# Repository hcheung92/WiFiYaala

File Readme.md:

WiFi Yaala
==========
Yaala = Yet Another Ambient Light Approach using an ESP8622 chip

Background
----------
Despite some early prototypes this is the third major attempt to create a fully featured and yet simple to control RGB LED system.  

Project Status
--------------
As a base we are using the nodeMCU core to provide a fully functional eLUA console. We are adding stuff specific for our application like a LED core.
Additionally, we add some optional nice to have features like the Domain Name support for the DHCP client.

It is currently in a VERY early state. Documentation does not yet exist. The only thing which is working right now is the driver support for APA102 and PCA9685 LEDs. Besides others, WS28XX LEDs (glitch free, using hardware support) are getting implemented right now.
Stay tuned...

Features
--------

1) Removed eLUA (nodemcu) modules
- PWM: we need the timer for the LEDs
- MQTT: currently no needed
- WS2812: we are doing it proper: 127bytes hardware FIFO support. No hitches or glitches...

2) Embedded web browser
/fsbrowse let's you browse the file system
/lua HTTP POST requests get interpreted. See lua/luaexec.html for more details on this.

3) Additional LUA stuff
- hostname.set() / hostname.get() let's you specify a hostname that will be transmitted to the DHCP server during a DHCP request. Execute the command BEFORE getting/renewing an IP, e.g. in the first line of init.lua
- led.XXXX see lua-folder and/or sourcecode for usage (for now, I am too lazy to document it ggg)

Requirements
-------------
GCC toolchain, see https://github.com/esp8266/esp8266-wiki/wiki

Building
--------
Goto firmware-lua and type "make && make flash"

Credits
----------
This work is based  on:

- Espressif SDK (http://bbs.espressif.com/viewforum.php?f=5)
- NodeMCU (https://github.com/nodemcu/nodemcu-firmware)
- eLUA (http://www.eluaproject.net/)
- and various other unnamed contributors

Due to frequent major changes in the code---especially in the SDK---everything is copied into this repo.

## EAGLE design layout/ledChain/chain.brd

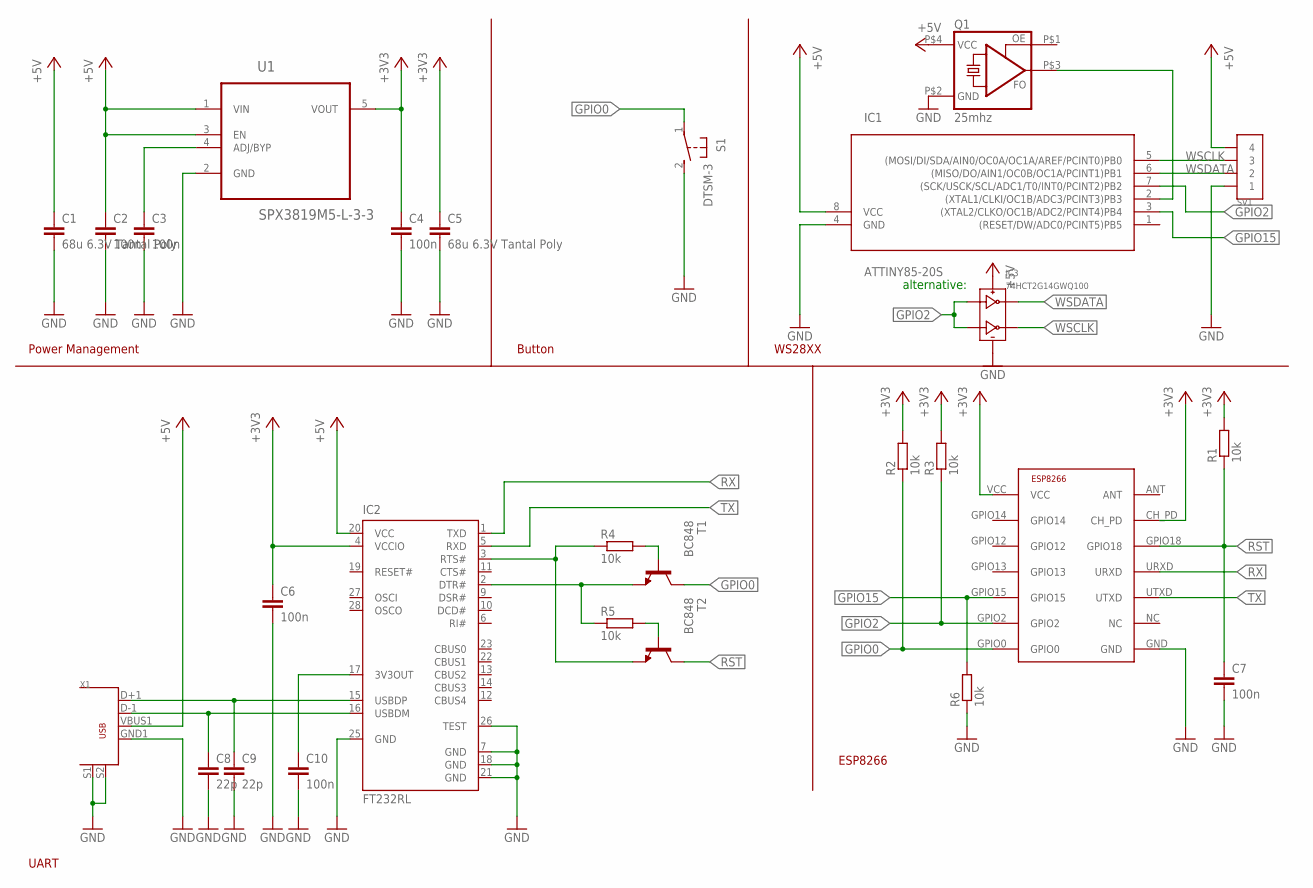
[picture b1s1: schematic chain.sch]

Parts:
C1, C5: 68u 6.3V Tantal Poly; C0805
C2, C3, C4, C6, C7, C10: 100n; C0603
C8, C9: 22p; C0603
IC1: ATTINY85-20S; SOIC8
IC2: FT232RL; SSOP28
IC3: 74HCT2G14GWQ100; SOT363
Q1: 25mhz; KC5032A
R1, R2, R3, R4, R5, R6: 10k; R0603
S1: DTSM-3
SV1: 1X4SMD-2.54LIEGEND
T1, T2: BC848; SOT23
U1: SPX3819M5-L-3-3; SOT95P280X145-5N
U$2: ESP8266; ESP-03
X1: USB-MALE-SMT

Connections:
+3V3: C4.1, C5.1, C6.1, IC2.4 (VCCIO), R1.2, R2.2, R3.2, U1.5 (VOUT), U$2.CH_PD, U$2.VCC
+5V: C1.1, C2.1, IC1.8 (VCC), IC2.20 (VCC), IC3.5 (VCC), Q1.P$4 (VCC), SV1.P$4 (4), U1.1 (VIN), U1.3 (EN), X1.VBUS1 (VBUS)
GND: C1.2, C2.2, C3.2, C4.2, C5.2, C6.2, C7.2, C8.2, C9.2, C10.2, IC1.4 (GND), IC2.7 (GND), IC2.18 (GND), IC2.21 (GND), IC2.25 (GND), IC2.26 (TEST), IC3.2 (GND), Q1.P$2 (GND), R6.1, S1.2, SV1.P$1 (1), U1.2 (GND), U$2.GND, X1.GND1 (GND), X1.S1, X1.S2
GPIO0: R2.1, S1.1, T1.3 (C), U$2.GPIO0
GPIO2: IC1.7 ((SCK/USCK/SCL/ADC1/T0/INT0/PCINT2)PB2), IC3.1 (1A), IC3.3 (2A), R3.1, U$2.GPIO2
GPIO15: IC1.3 ((XTAL2/CLKO/OC1B/ADC2/PCINT4)PB4), R6.2, U$2.GPIO15
unnamed: IC2.3 (RTS#), R4.1, T2.2 (E)
unnamed: IC1.2 ((XTAL1/CLKI/OC1B/ADC3/PCINT3)PB3), Q1.P$3 (FO)
unnamed: C9.1, IC2.15 (USBDP), X1.D+1 (D+)
unnamed: C8.1, IC2.16 (USBDM), X1.D-1 (D-)
unnamed: IC2.2 (DTR#), R5.1, T1.2 (E)
unnamed: R4.2, T1.1 (B)
unnamed: R5.2, T2.1 (B)
unnamed: C10.1, IC2.17 (3V3OUT)
unnamed: C3.1, U1.4 (ADJ/BYP)
RST: C7.1, R1.1, T2.3 (C), U$2.GPIO18
RX: IC2.1 (TXD), U$2.URXD
TX: IC2.5 (RXD), U$2.UTXD
WSCLK: IC1.5 ((MOSI/DI/SDA/AIN0/OC0A/OC1A/AREF/PCINT0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), IC3.4 (2Y), SV1.P$3 (3)
WSDATA: IC1.6 ((MISO/DO/AIN1/OC0B/OC1A/PCINT1)PB1), IC3.6 (1Y), SV1.P$2 (2)

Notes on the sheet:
Power Management
Button
UART
ESP8266
WS28XX
alternative:

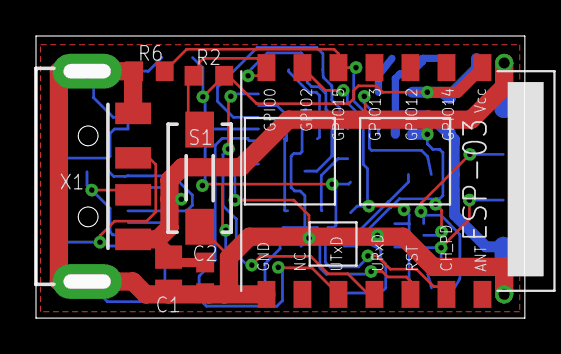
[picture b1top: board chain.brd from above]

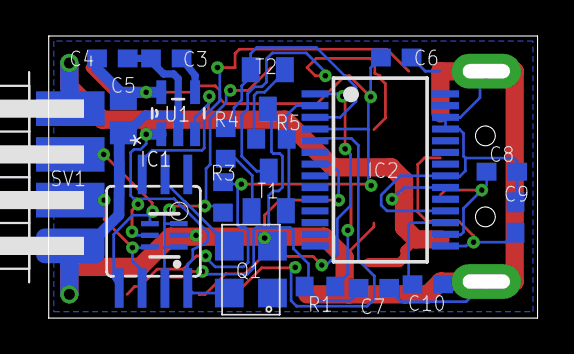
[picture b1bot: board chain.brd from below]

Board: 2 copper layers, 27.2 x 15.7 mm, 27 parts (20 on the bottom side), 20 nets.

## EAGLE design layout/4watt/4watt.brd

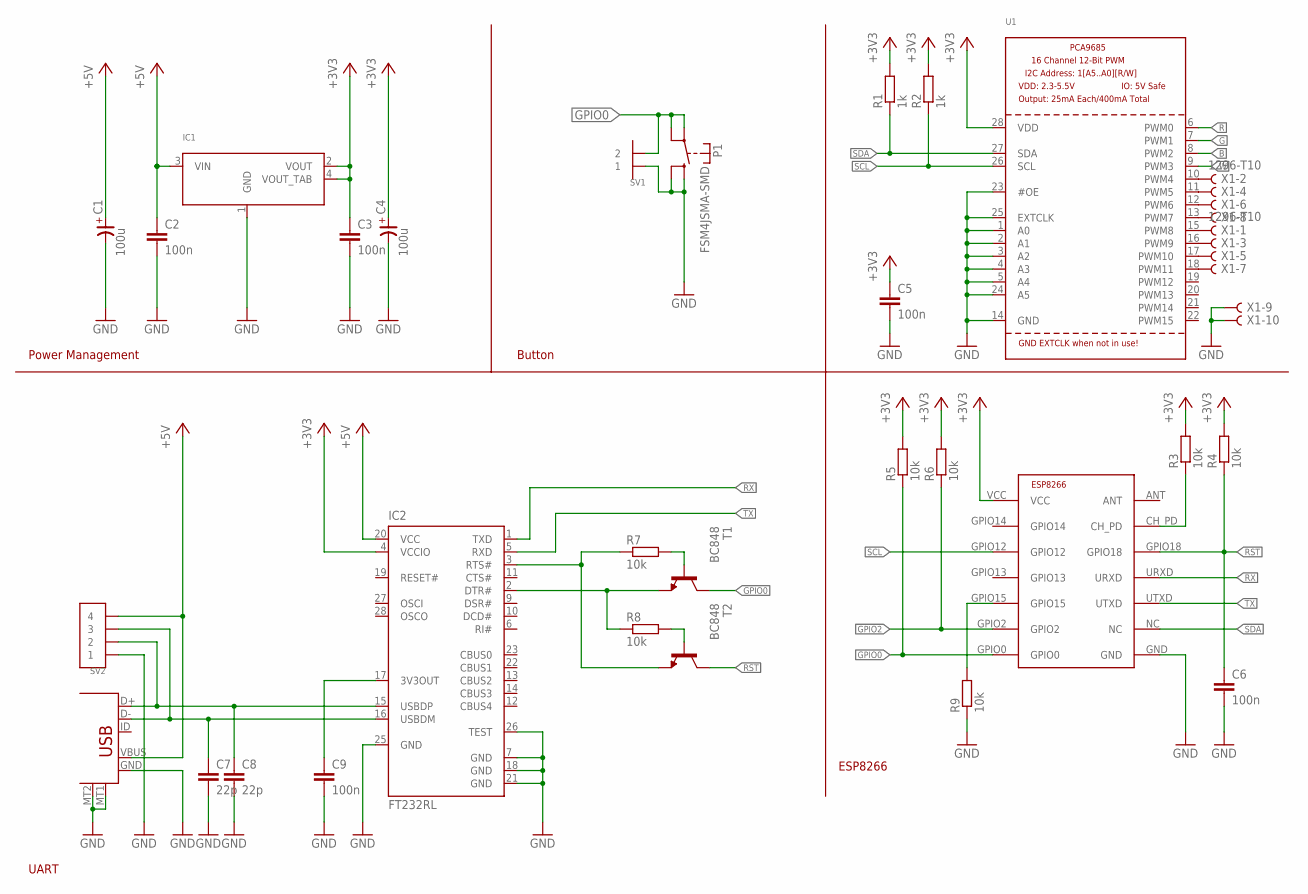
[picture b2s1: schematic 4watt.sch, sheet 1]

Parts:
C1, C4: 100u; 7343-TE-D
C2, C3, C5, C6, C9: 100n; C0603
C7, C8: 22p; C0603
IC1: LM1117IMP; SOT223
IC2: FT232RL; SSOP28
P1: FSM4JSMA-SMD
R1, R2: 1k; R0603
R3, R4, R5, R6, R7, R8, R9: 10k; R0603
SV1: 1X2SMD-2.54LIEGEND
SV2: 1X4SMD-2.54LIEGEND
T1, T2: BC848; SOT23
U1: PCA9685; TSSOP28
U$1: ESP8266; ESP-03
X1: 1296-T10; 1296-10
X2: USB-B; USB-MICROB

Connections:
+3V3: C3.1, C4.+, C5.1, IC1.2 (VOUT), IC1.4 (VOUT_TAB), IC2.4 (VCCIO), R1.2, R2.2, R3.2, R4.2, R5.2, R6.2, U1.28 (VDD), U$1.VCC
+5V: C1.+, C2.1, IC1.3 (VIN), IC2.20 (VCC), SV2.P$4 (4), X2.VBUS; also elsewhere on the board
B: U1.8 (PWM2); also elsewhere on the board
G: U1.7 (PWM1); also elsewhere on the board
GND: C1.-, C2.2, C3.2, C4.-, C5.2, C6.2, C7.2, C8.2, C9.2, IC1.1 (GND), IC2.7 (GND), IC2.18 (GND), IC2.21 (GND), IC2.25 (GND), IC2.26 (TEST), P1.P$3 (S), P1.P$4 (S), R9.1, SV1.P$1 (1), SV2.P$1 (1), U1.1 (A0), U1.2 (A1), U1.3 (A2), U1.4 (A3), U1.5 (A4), U1.14 (GND), U1.23 (#OE), U1.24 (A5), U1.25 (EXTCLK), U$1.GND, X1.9, X1.10, X2.GND, X2.MT1, X2.MT2; also elsewhere on the board
GPIO0: P1.P$1, P1.P$2, R5.1, SV1.P$2 (2), T1.3 (C), U$1.GPIO0
GPIO2: R6.1, U$1.GPIO2; also elsewhere on the board
GPIO15: R9.2, U$1.GPIO15
unnamed: IC2.3 (RTS#), R7.1, T2.2 (E)
unnamed: R3.1, U$1.CH_PD
unnamed: C8.1, IC2.15 (USBDP), SV2.P$2 (2), X2.D+
unnamed: C7.1, IC2.16 (USBDM), SV2.P$3 (3), X2.D-
unnamed: IC2.2 (DTR#), R8.1, T1.2 (E)
unnamed: R7.2, T1.1 (B)
unnamed: R8.2, T2.1 (B)
unnamed: C9.1, IC2.17 (3V3OUT)
unnamed: U1.10 (PWM4), X1.2
unnamed: U1.11 (PWM5), X1.4
unnamed: U1.12 (PWM6), X1.6
unnamed: U1.13 (PWM7), X1.8
unnamed: U1.15 (PWM8), X1.1
unnamed: U1.16 (PWM9), X1.3
unnamed: U1.17 (PWM10), X1.5
unnamed: U1.18 (PWM11), X1.7
R: U1.6 (PWM0); also elsewhere on the board
RST: C6.1, R4.1, T2.3 (C), U$1.GPIO18
RX: IC2.1 (TXD), U$1.URXD
SCL: R2.1, U1.26 (SCL), U$1.GPIO12
SDA: R1.1, U1.27 (SDA), U$1.NC
TX: IC2.5 (RXD), U$1.UTXD
W: U1.9 (PWM3); also elsewhere on the board

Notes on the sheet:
Power Management
Button
UART
ESP8266

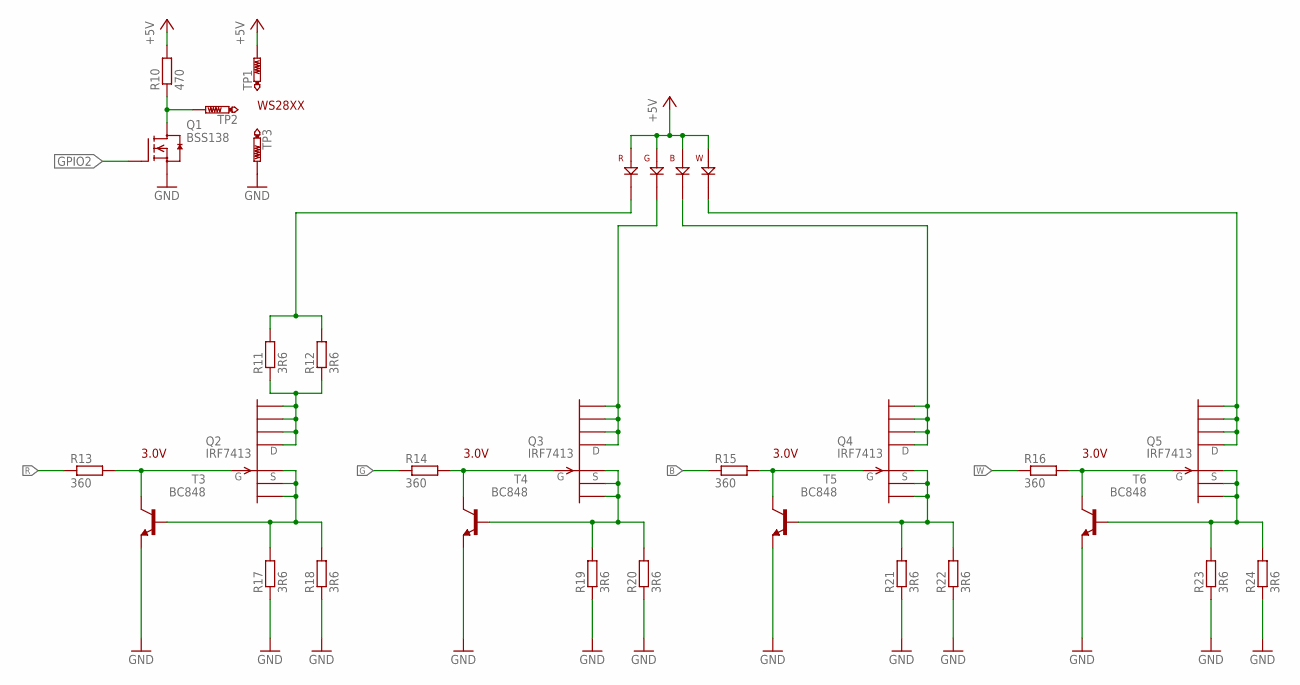
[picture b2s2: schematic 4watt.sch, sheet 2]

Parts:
LED1: JH-4RGBW14G30-E2A
Q1: BSS138; SOT23
Q2, Q3, Q4, Q5: IRF7413; SO-8
R10: 470; R0603
R11, R12, R17, R18, R19, R20, R21, R22, R23, R24: 3R6; M1206
R13, R14, R15, R16: 360; R0603
T3, T4, T5, T6: BC848; SOT23
TP1, TP3: PTR1B2,54; B2,54
TP2: PTR1B1,27; B1,27

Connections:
+5V: LED1.B+, LED1.G+, LED1.R+, LED1.W+, R10.2, TP1.TP; also elsewhere on the board
B: R15.1; also elsewhere on the board
G: R14.1; also elsewhere on the board
GND: Q1.2 (S), R17.1, R18.1, R19.1, R20.1, R21.1, R22.1, R23.1, R24.1, T3.2 (E), T4.2 (E), T5.2 (E), T6.2 (E), TP3.TP; also elsewhere on the board
GPIO2: Q1.1 (G); also elsewhere on the board
unnamed: Q1.3 (D), R10.1, TP2.TP
unnamed: Q2.1 (S), Q2.2 (S1), Q2.3 (S2), R17.2, R18.2, T3.1 (B)
unnamed: Q2.5 (D), Q2.6 (D1), Q2.7 (D2), Q2.8 (D3), R11.1, R12.1
unnamed: Q5.4 (G), R16.2, T6.3 (C)
unnamed: Q5.1 (S), Q5.2 (S1), Q5.3 (S2), R23.2, R24.2, T6.1 (B)
unnamed: LED1.W-, Q5.5 (D), Q5.6 (D1), Q5.7 (D2), Q5.8 (D3)
unnamed: Q2.4 (G), R13.2, T3.3 (C)
unnamed: LED1.R-, R11.2, R12.2
unnamed: Q3.4 (G), R14.2, T4.3 (C)
unnamed: Q3.1 (S), Q3.2 (S1), Q3.3 (S2), R19.2, R20.2, T4.1 (B)
unnamed: LED1.G-, Q3.5 (D), Q3.6 (D1), Q3.7 (D2), Q3.8 (D3)
unnamed: Q4.4 (G), R15.2, T5.3 (C)
unnamed: Q4.1 (S), Q4.2 (S1), Q4.3 (S2), R21.2, R22.2, T5.1 (B)
unnamed: LED1.B-, Q4.5 (D), Q4.6 (D1), Q4.7 (D2), Q4.8 (D3)
R: R13.1; also elsewhere on the board
W: R16.1; also elsewhere on the board

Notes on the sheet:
3.0V
WS28XX

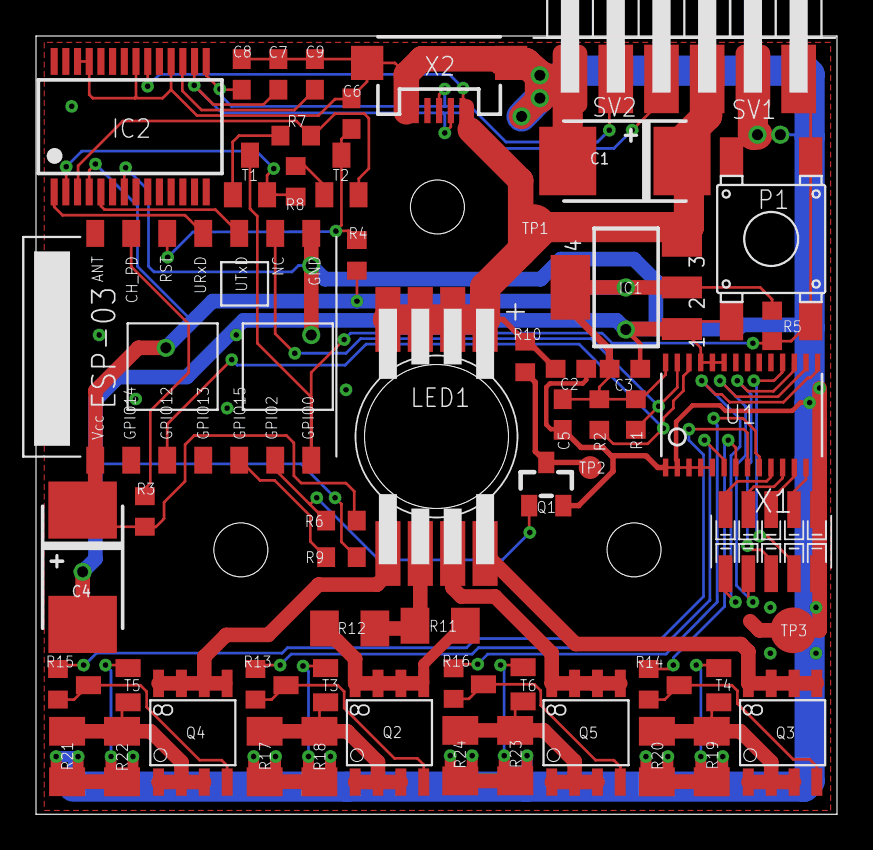
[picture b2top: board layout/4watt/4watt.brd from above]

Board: 2 copper layers, 44.5 x 43.2 mm, 57 parts (0 on the bottom side), 45 nets.

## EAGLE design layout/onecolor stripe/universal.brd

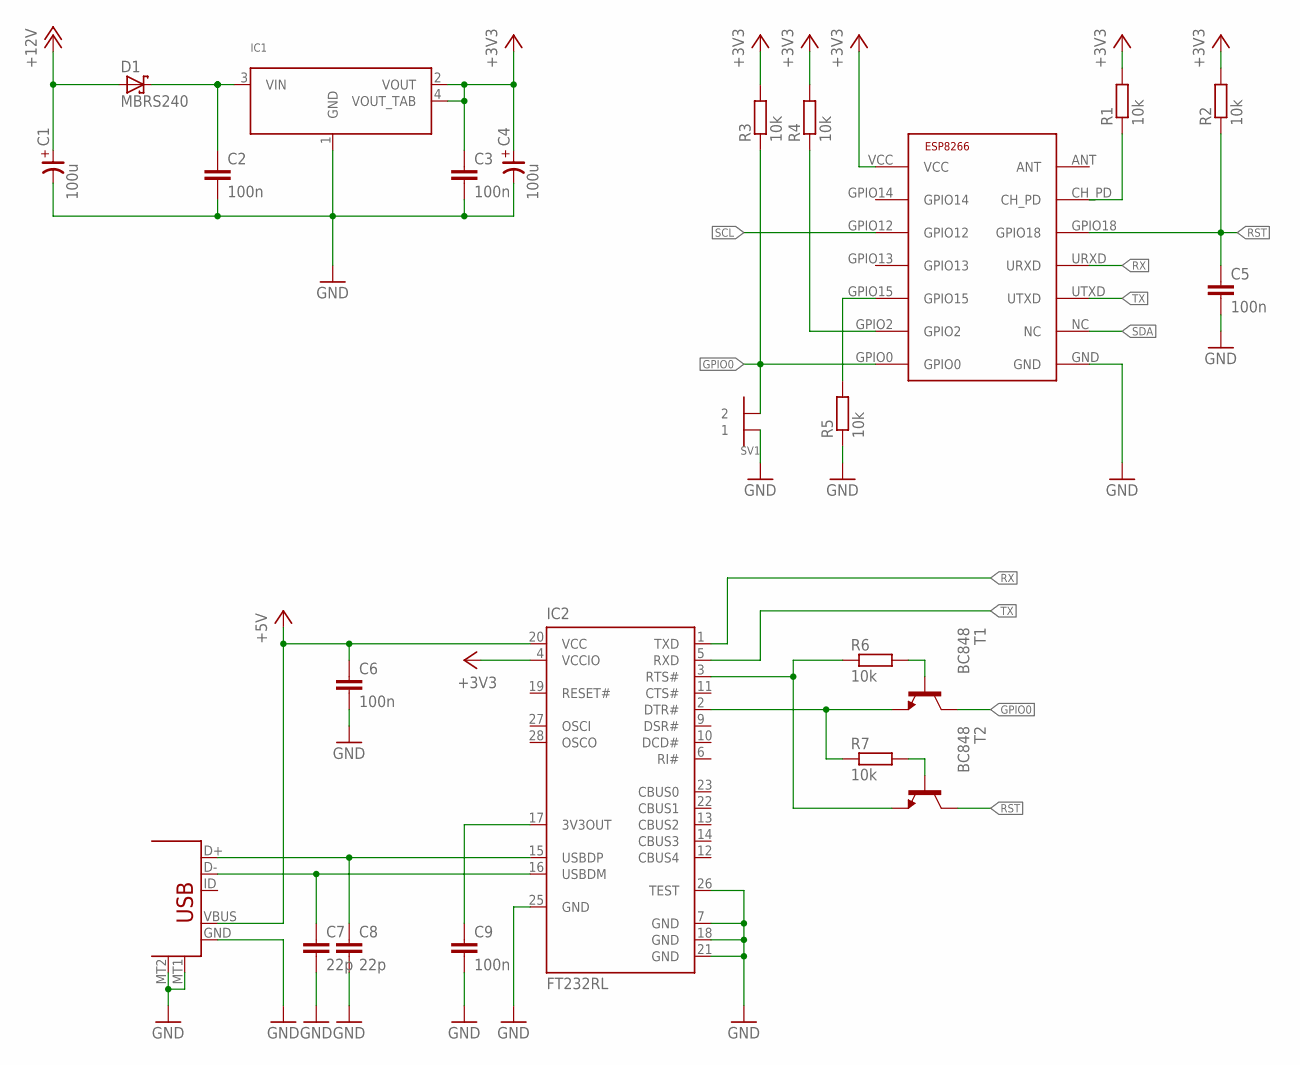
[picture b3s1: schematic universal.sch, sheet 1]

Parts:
C1, C4: 100u; 7343-TE-D
C2, C3, C5, C6, C9: 100n; C0603
C7, C8: 22p; C0603
D1: MBRS240; SMB
IC1: LM1117IMP; SOT223
IC2: FT232RL; SSOP28
R1, R2, R3, R4, R5, R6, R7: 10k; R0603
SV1: 1X2SMD-2.54LIEGEND
T1, T2: BC848; SOT23
U$1: ESP8266; ESP-03
X1: USB-B; USB-MICROB

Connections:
+3V3: C3.1, C4.+, IC1.2 (VOUT), IC1.4 (VOUT_TAB), IC2.4 (VCCIO), R1.2, R2.2, R3.2, R4.2, U$1.VCC; also elsewhere on the board
+5V: C6.1, IC2.20 (VCC), X1.VBUS
+12V: C1.+, D1.A; also elsewhere on the board
D+: C8.1, IC2.15 (USBDP), X1.D+
D-: C7.1, IC2.16 (USBDM), X1.D-
GND: C1.-, C2.2, C3.2, C4.-, C5.2, C6.2, C7.2, C8.2, C9.2, IC1.1 (GND), IC2.7 (GND), IC2.18 (GND), IC2.21 (GND), IC2.25 (GND), IC2.26 (TEST), R5.1, SV1.P$1 (1), U$1.GND, X1.GND, X1.MT1, X1.MT2; also elsewhere on the board
GPIO0: R3.1, SV1.P$2 (2), T1.3 (C), U$1.GPIO0
GPIO15: R5.2, U$1.GPIO15
unnamed: IC2.3 (RTS#), R6.1, T2.2 (E)
unnamed: IC2.2 (DTR#), R7.1, T1.2 (E)
unnamed: R6.2, T1.1 (B)
unnamed: R7.2, T2.1 (B)
unnamed: R1.1, U$1.CH_PD
unnamed: C9.1, IC2.17 (3V3OUT)
unnamed: R4.1, U$1.GPIO2
unnamed: C2.1, D1.C, IC1.3 (VIN)
RST: C5.1, R2.1, T2.3 (C), U$1.GPIO18
RX: IC2.1 (TXD), U$1.URXD
SCL: U$1.GPIO12; also elsewhere on the board
SDA: U$1.NC; also elsewhere on the board
TX: IC2.5 (RXD), U$1.UTXD

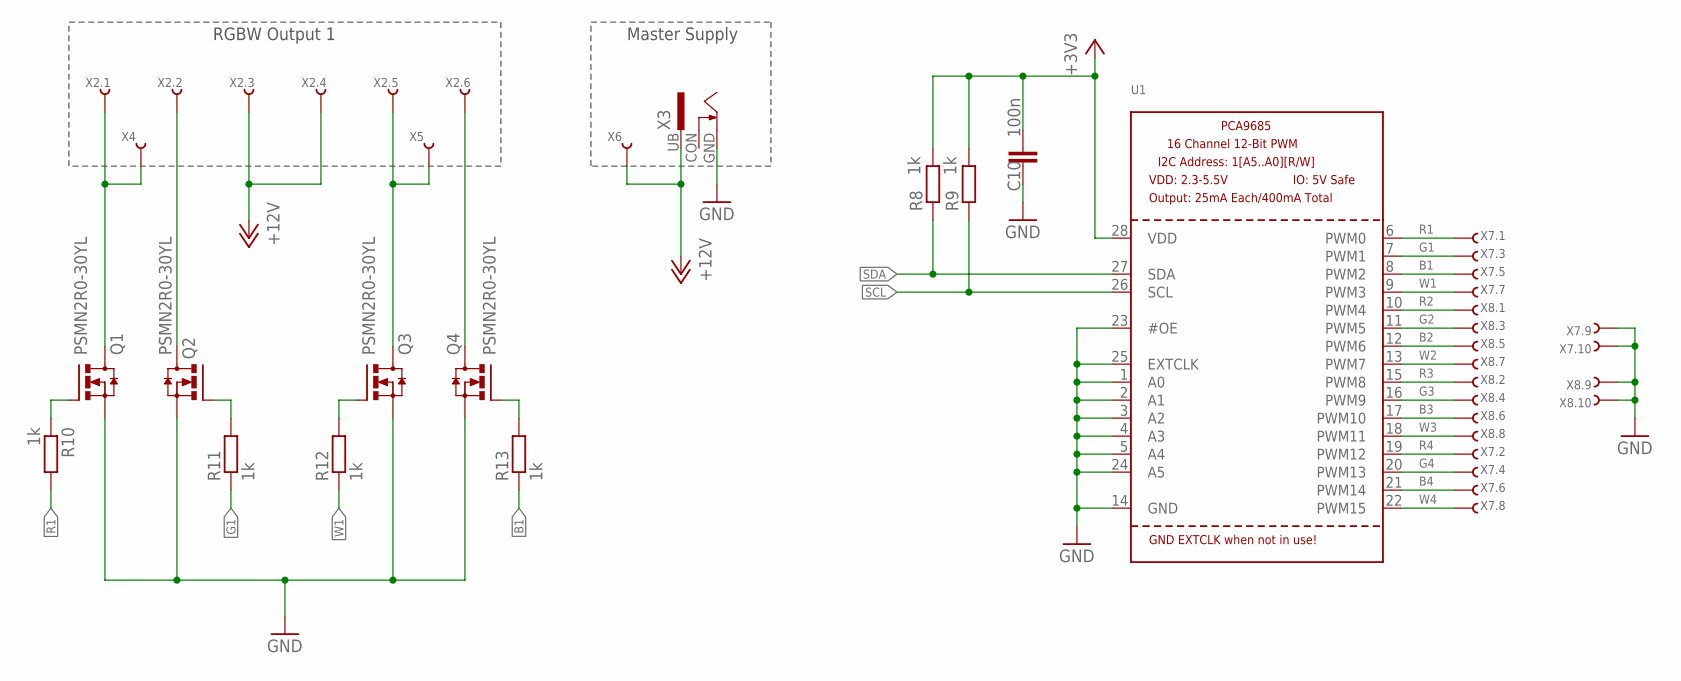
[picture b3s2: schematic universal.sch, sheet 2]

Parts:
C10: 100n; C0603
Q1, Q2, Q3, Q4: PSMN2R0-30YL; SOT669
R8, R9, R10, R11, R12, R13: 1k; R0603
U1: PCA9685; TSSOP28
X2: 6PIN_MDF6-6DP-3.5DS; MDF6-6DP-3.5DS
X3: HSB_2,5_6,3
X4, X5, X6: 1PIN_SCHRAUBKLEMME
X7, X8: 10PIN_LEOTRONICS_1296-10; 1296-10

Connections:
+3V3: C10.1, R8.2, R9.2, U1.28 (VDD); also elsewhere on the board
+12V: X2.3, X2.4, X3.UB (1), X6.1; also elsewhere on the board
B1: R13.1, U1.8 (PWM2), X7.5
B2: U1.12 (PWM6), X8.5; also elsewhere on the board
B3: U1.17 (PWM10), X8.6; also elsewhere on the board
B4: U1.21 (PWM14), X7.6; also elsewhere on the board
G1: R11.1, U1.7 (PWM1), X7.3
G2: U1.11 (PWM5), X8.3; also elsewhere on the board
G3: U1.16 (PWM9), X8.4; also elsewhere on the board
G4: U1.20 (PWM13), X7.4; also elsewhere on the board
GND: C10.2, Q1.1 (S), Q1.2 (S), Q1.3 (S), Q2.1 (S), Q2.2 (S), Q2.3 (S), Q3.1 (S), Q3.2 (S), Q3.3 (S), Q4.1 (S), Q4.2 (S), Q4.3 (S), U1.1 (A0), U1.2 (A1), U1.3 (A2), U1.4 (A3), U1.5 (A4), U1.14 (GND), U1.23 (#OE), U1.24 (A5), U1.25 (EXTCLK), X3.GND (2), X7.9, X7.10, X8.9, X8.10; also elsewhere on the board
unnamed: Q1.MB (D), X2.1, X4.1
unnamed: Q2.MB (D), X2.2
unnamed: Q4.MB (D), X2.6
unnamed: Q3.MB (D), X2.5, X5.1
unnamed: Q1.4 (G), R10.1
unnamed: Q2.4 (G), R11.2
unnamed: Q3.4 (G), R12.2
unnamed: Q4.4 (G), R13.2
R1: R10.2, U1.6 (PWM0), X7.1
R2: U1.10 (PWM4), X8.1; also elsewhere on the board
R3: U1.15 (PWM8), X8.2; also elsewhere on the board
R4: U1.19 (PWM12), X7.2; also elsewhere on the board
SCL: R9.1, U1.26 (SCL); also elsewhere on the board
SDA: R8.1, U1.27 (SDA); also elsewhere on the board
W1: R12.1, U1.9 (PWM3), X7.7
W2: U1.13 (PWM7), X8.7; also elsewhere on the board
W3: U1.18 (PWM11), X8.8; also elsewhere on the board
W4: U1.22 (PWM15), X7.8; also elsewhere on the board

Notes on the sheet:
RGBW Output 1
Master Supply

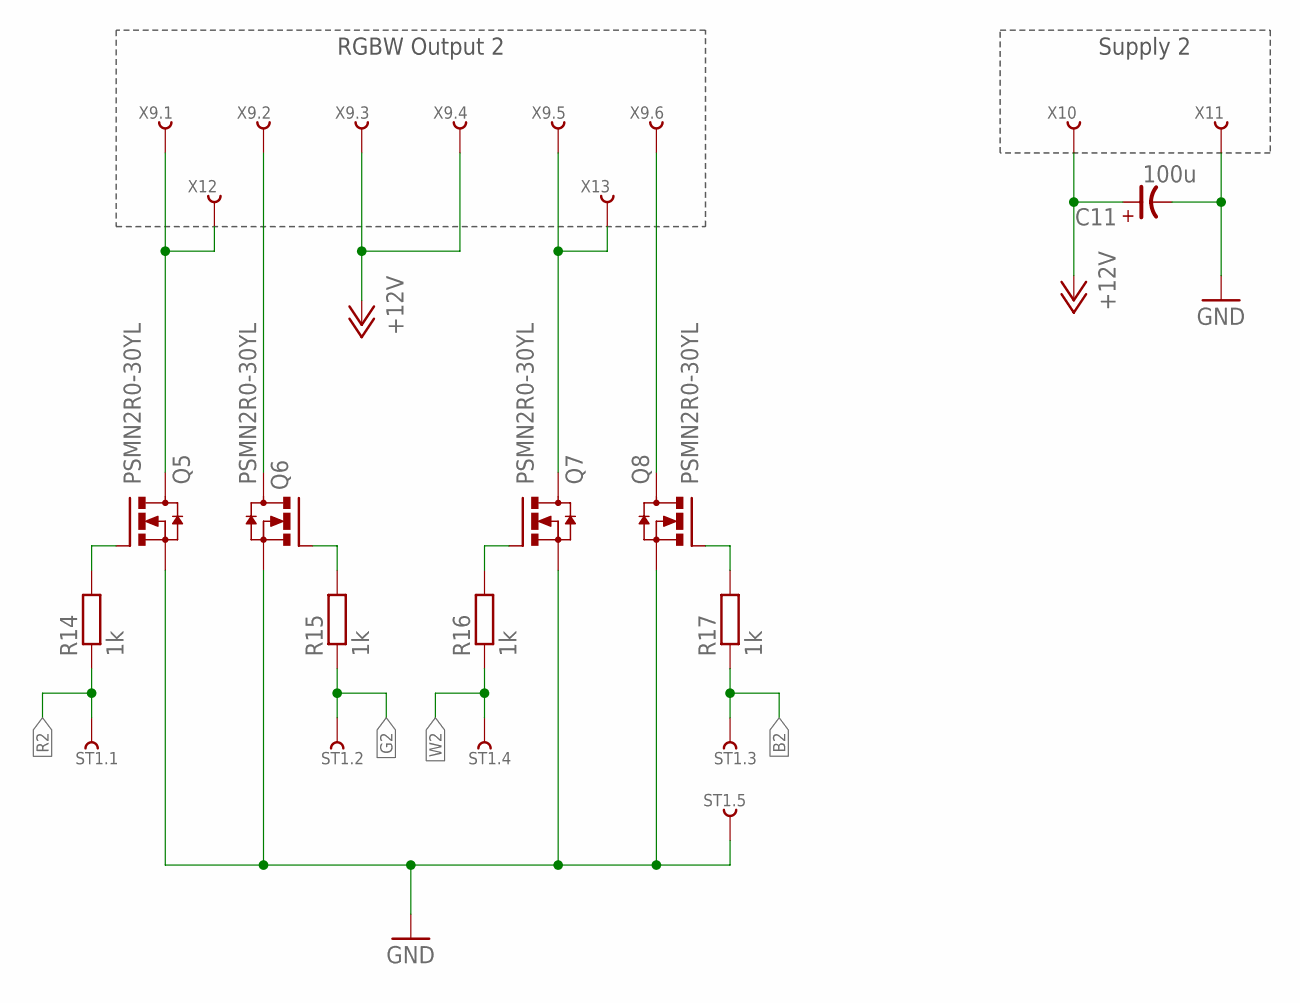
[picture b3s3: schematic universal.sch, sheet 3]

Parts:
C11: 100u; 7343-TE-D
Q5, Q6, Q7, Q8: PSMN2R0-30YL; SOT669
R14, R15, R16, R17: 1k; R0603
ST1: 5PIN_STIFTLEISTE_1,27MM
X9: 6PIN_MDF6-6DP-3.5DS; MDF6-6DP-3.5DS
X10, X11, X12, X13: 1PIN_SCHRAUBKLEMME

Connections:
+12V: C11.+, X9.3, X9.4, X10.1; also elsewhere on the board
B2: R17.1, ST1.3; also elsewhere on the board
G2: R15.1, ST1.2; also elsewhere on the board
GND: C11.-, Q5.1 (S), Q5.2 (S), Q5.3 (S), Q6.1 (S), Q6.2 (S), Q6.3 (S), Q7.1 (S), Q7.2 (S), Q7.3 (S), Q8.1 (S), Q8.2 (S), Q8.3 (S), ST1.5, X11.1; also elsewhere on the board
unnamed: Q5.MB (D), X9.1, X12.1
unnamed: Q6.MB (D), X9.2
unnamed: Q7.MB (D), X9.5, X13.1
unnamed: Q8.MB (D), X9.6
unnamed: Q6.4 (G), R15.2
unnamed: Q7.4 (G), R16.2
unnamed: Q8.4 (G), R17.2
unnamed: Q5.4 (G), R14.2
R2: R14.1, ST1.1; also elsewhere on the board
W2: R16.1, ST1.4; also elsewhere on the board

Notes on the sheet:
RGBW Output 2
Supply 2

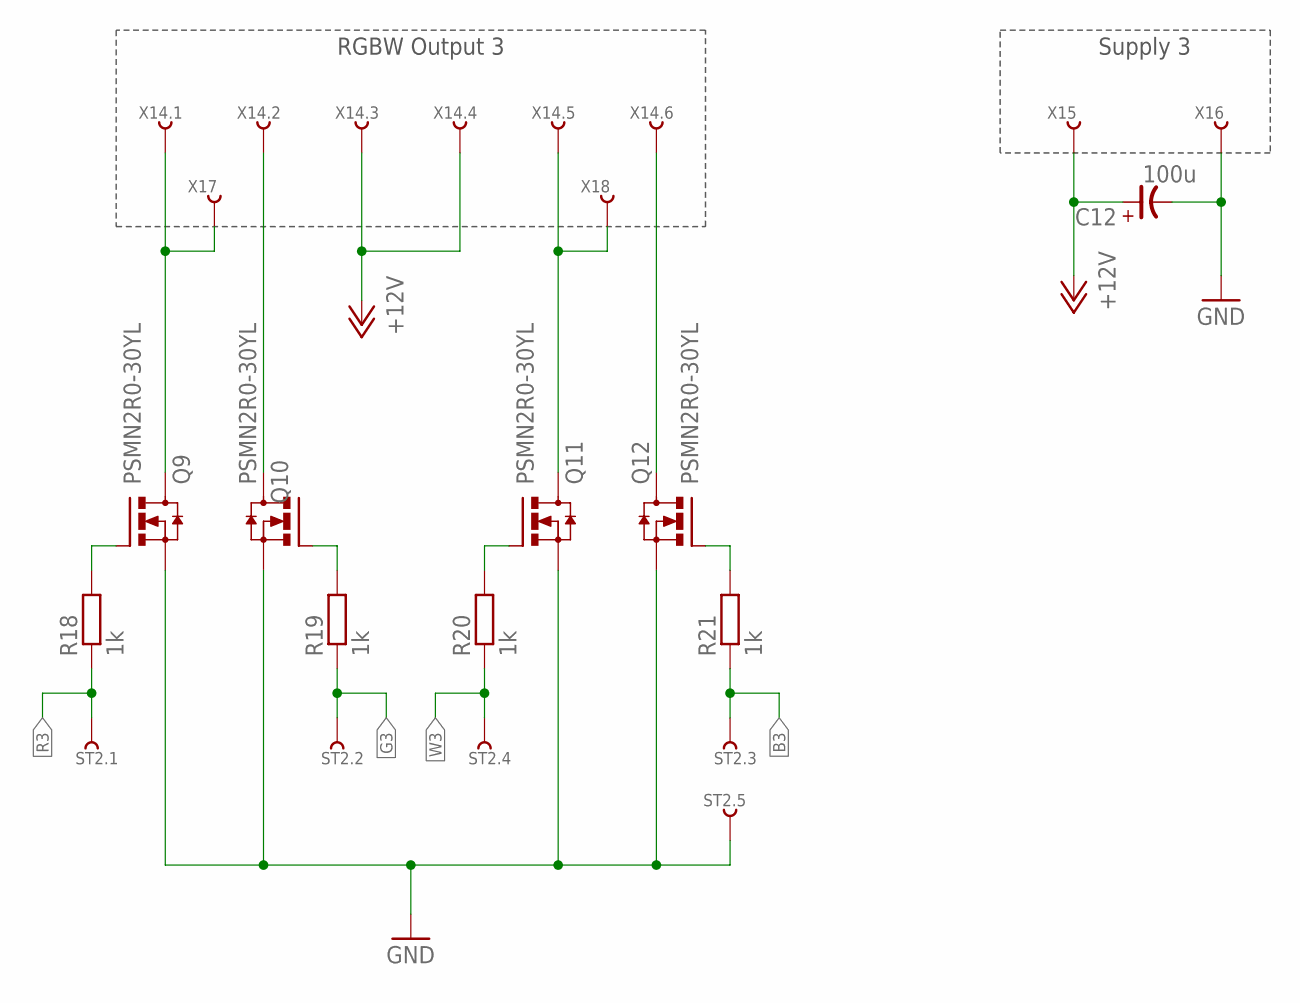
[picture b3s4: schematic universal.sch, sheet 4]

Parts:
C12: 100u; 7343-TE-D
Q9, Q10, Q11, Q12: PSMN2R0-30YL; SOT669
R18, R19, R20, R21: 1k; R0603
ST2: 5PIN_STIFTLEISTE_1,27MM
X14: 6PIN_MDF6-6DP-3.5DS; MDF6-6DP-3.5DS
X15, X16, X17, X18: 1PIN_SCHRAUBKLEMME

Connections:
+12V: C12.+, X14.3, X14.4, X15.1; also elsewhere on the board
B3: R21.1, ST2.3; also elsewhere on the board
G3: R19.1, ST2.2; also elsewhere on the board
GND: C12.-, Q9.1 (S), Q9.2 (S), Q9.3 (S), Q10.1 (S), Q10.2 (S), Q10.3 (S), Q11.1 (S), Q11.2 (S), Q11.3 (S), Q12.1 (S), Q12.2 (S), Q12.3 (S), ST2.5, X16.1; also elsewhere on the board
unnamed: Q9.MB (D), X14.1, X17.1
unnamed: Q10.MB (D), X14.2
unnamed: Q11.MB (D), X14.5, X18.1
unnamed: Q12.MB (D), X14.6
unnamed: Q10.4 (G), R19.2
unnamed: Q11.4 (G), R20.2
unnamed: Q12.4 (G), R21.2
unnamed: Q9.4 (G), R18.2
R3: R18.1, ST2.1; also elsewhere on the board
W3: R20.1, ST2.4; also elsewhere on the board

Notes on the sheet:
RGBW Output 3
Supply 3

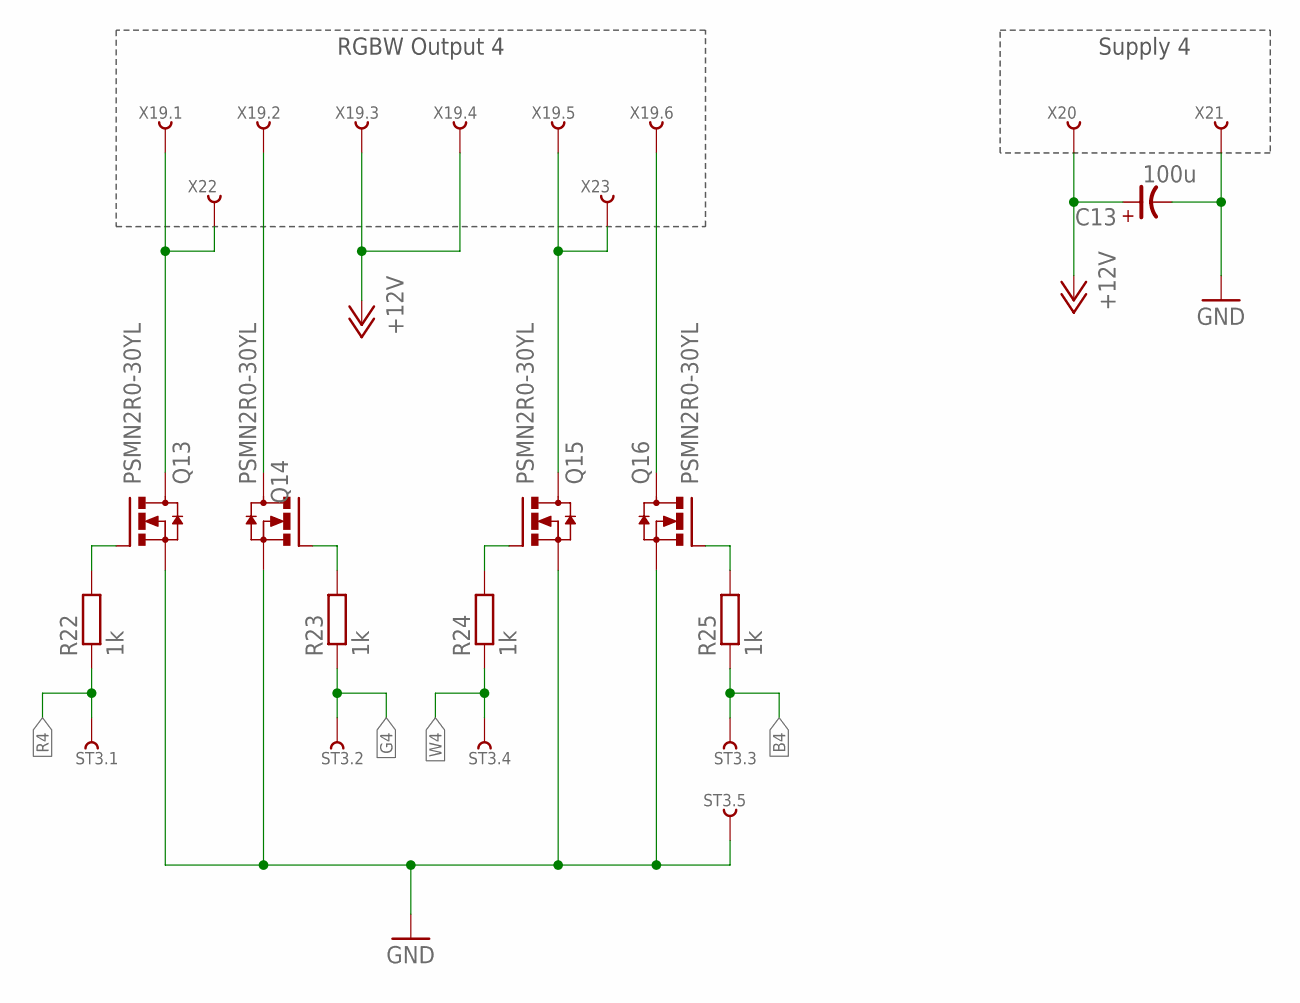
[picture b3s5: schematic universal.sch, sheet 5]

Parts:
C13: 100u; 7343-TE-D
Q13, Q14, Q15, Q16: PSMN2R0-30YL; SOT669
R22, R23, R24, R25: 1k; R0603
ST3: 5PIN_STIFTLEISTE_1,27MM
X19: 6PIN_MDF6-6DP-3.5DS; MDF6-6DP-3.5DS
X20, X21, X22, X23: 1PIN_SCHRAUBKLEMME

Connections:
+12V: C13.+, X19.3, X19.4, X20.1; also elsewhere on the board
B4: R25.1, ST3.3; also elsewhere on the board
G4: R23.1, ST3.2; also elsewhere on the board
GND: C13.-, Q13.1 (S), Q13.2 (S), Q13.3 (S), Q14.1 (S), Q14.2 (S), Q14.3 (S), Q15.1 (S), Q15.2 (S), Q15.3 (S), Q16.1 (S), Q16.2 (S), Q16.3 (S), ST3.5, X21.1; also elsewhere on the board
unnamed: Q13.MB (D), X19.1, X22.1
unnamed: Q14.MB (D), X19.2
unnamed: Q15.MB (D), X19.5, X23.1
unnamed: Q16.MB (D), X19.6
unnamed: Q14.4 (G), R23.2
unnamed: Q15.4 (G), R24.2
unnamed: Q16.4 (G), R25.2
unnamed: Q13.4 (G), R22.2
R4: R22.1, ST3.1; also elsewhere on the board
W4: R24.1, ST3.4; also elsewhere on the board

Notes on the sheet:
RGBW Output 4
Supply 4

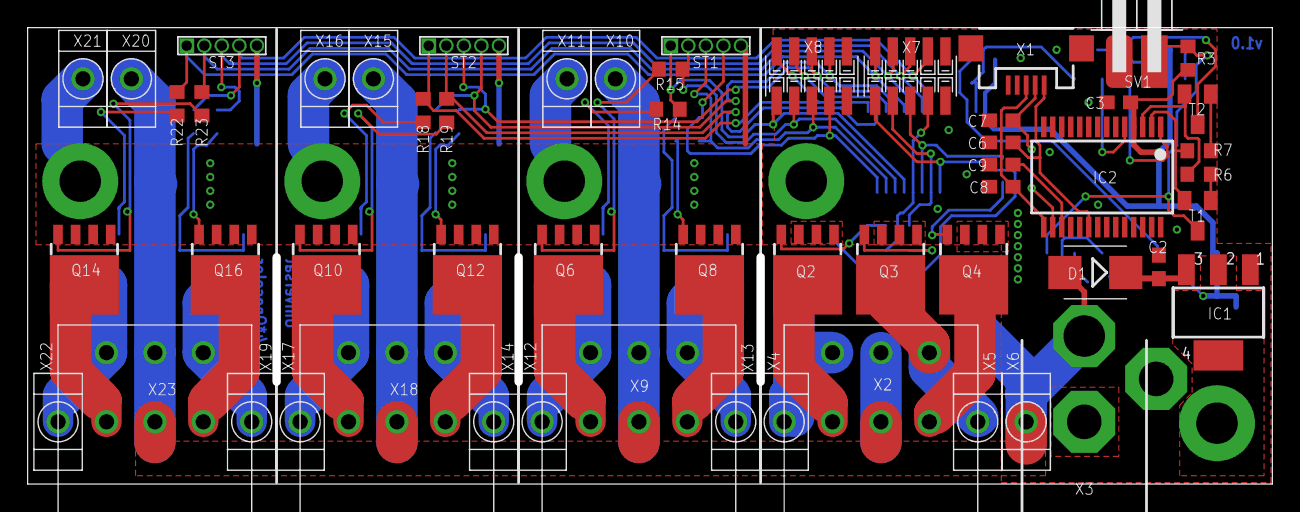
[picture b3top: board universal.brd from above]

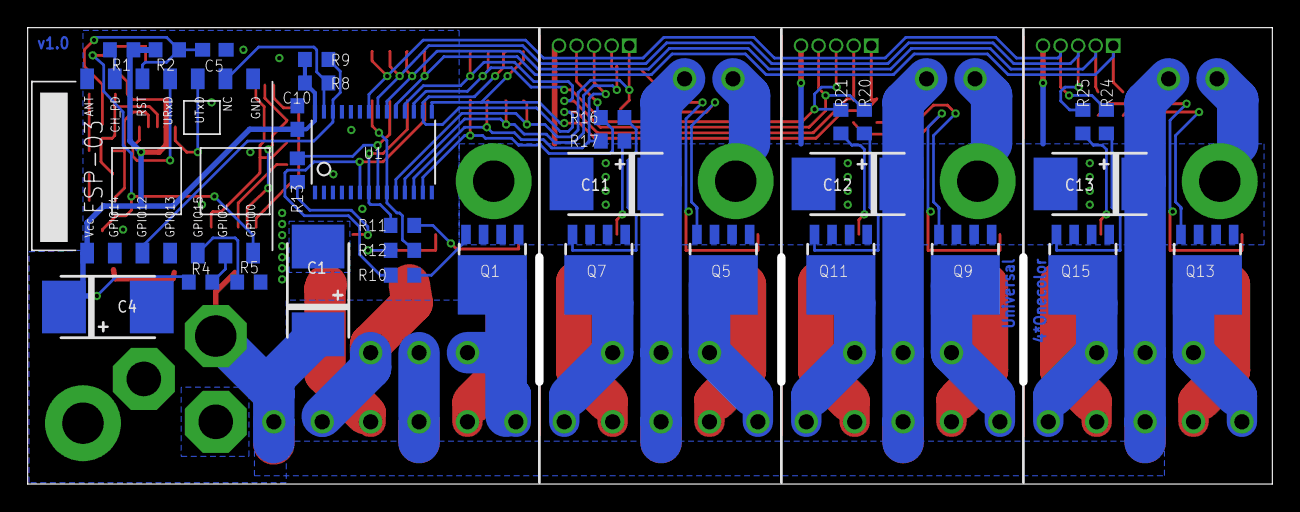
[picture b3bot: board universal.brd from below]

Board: 2 copper layers, 90.0 x 33.0 mm, 88 parts (32 on the bottom side), 69 nets.

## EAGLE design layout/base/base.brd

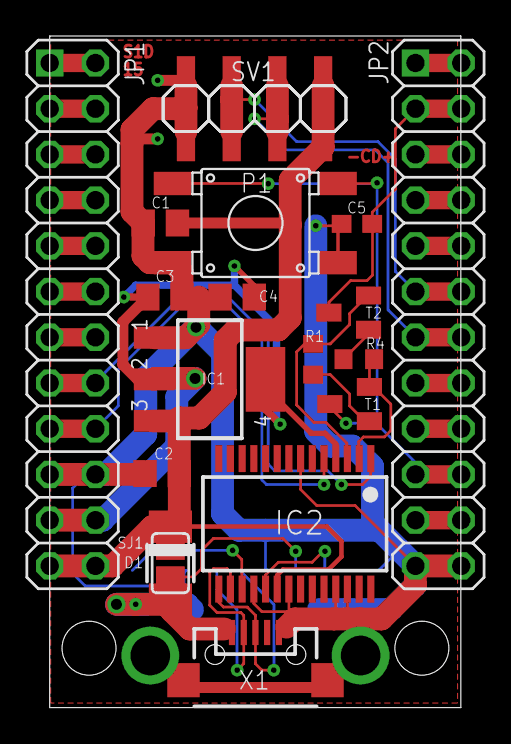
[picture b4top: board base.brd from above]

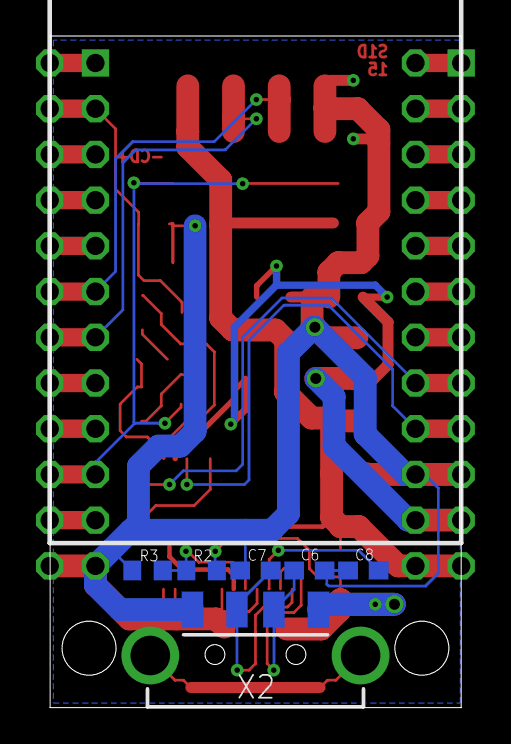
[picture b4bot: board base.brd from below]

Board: 2 copper layers, 22.8 x 37.3 mm, 25 parts (6 on the bottom side), 32 nets.

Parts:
C1, C2, C3, C4: 22u; C0805
C5, C8: 100n; C0603
C6, C7: 22p; C0603
D1: SK24A; DO-214AC
IC1: SOT223
IC2: FT232RL; SSOP28
JP1, JP2: 2X12
P1: FSM4JSMA-SMD
R1, R3, R4: 10k; R0603
R2: 4k7; R0603
SJ1: SJ
SV1, SV2: 1X4SMD-2.54
T1, T2: BC848; SOT23
X1: USB-B; USB-MICROB
X2: USB-MALE-SMT

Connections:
+3V3: C3.1, C4.1, IC1.2, IC1.4, IC2.4, JP1.21, JP1.22
+5V: C1.1, C2.1, D1.C, IC1.3, IC2.20, JP1.23, JP1.24, SJ1.2, SV1.1, SV2.4
CI: JP2.11, JP2.12, SV1.3, SV2.2
DI: JP2.13, JP2.14, SV1.2, SV2.3
GND: C1.2, C2.2, C3.2, C4.2, C5.2, C6.2, C7.2, C8.2, IC1.1, IC2.7, IC2.18, IC2.21, IC2.25, IC2.26, JP1.19, JP1.20, JP2.23, JP2.24, P1.P$3, P1.P$4, R3.1, SV1.4, SV2.1, X1.GND, X1.MT1, X1.MT2, X2.GND1, X2.S1, X2.S2
GPIO0: JP2.19, JP2.20, P1.P$1, P1.P$2, T1.3
unnamed: IC2.3, R1.1, T2.2
unnamed: D1.A, R2.2, SJ1.1, X1.VBUS, X2.VBUS1
unnamed: C7.1, IC2.15, X1.D+, X2.D+1
unnamed: C6.1, IC2.16, X1.D-, X2.D-1
unnamed: IC2.2, R4.1, T1.2
unnamed: IC2.19, R2.1, R3.2
unnamed: R1.2, T1.1
unnamed: R4.2, T2.1
unnamed: JP1.3, JP1.4
unnamed: C8.1, IC2.17
unnamed: JP1.5, JP1.6
unnamed: JP1.7, JP1.8
unnamed: JP1.9, JP1.10
unnamed: JP1.11, JP1.12
unnamed: JP1.13, JP1.14
unnamed: JP2.1, JP2.2
unnamed: JP2.5, JP2.6
unnamed: JP2.7, JP2.8
unnamed: JP2.9, JP2.10
unnamed: JP2.15, JP2.16
unnamed: JP2.17, JP2.18
RST: C5.1, JP2.3, JP2.4, T2.3
RX: IC2.1, JP1.15, JP1.16
SSL: JP2.21, JP2.22
SSR: JP1.1, JP1.2
TX: IC2.5, JP1.17, JP1.18

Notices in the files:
parts and their libraries:
m-pad-2.1: License : GNU General Public License version 2 (see bottom)
